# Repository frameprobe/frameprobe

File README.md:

# frameprobe

End-to-end display latency measurement: the time from a mouse input (click or
movement) to a visible change on screen, measured with a photodiode strapped to
the monitor.

**How it works:**

- An RP2040 sends a USB HID mouse click (or, in move mode, a mouse movement)
- The input causes a brightness change on the monitor under test (any application works, as long as the brightness difference is big enough)
- The photodiode picks up the change
- The RP2040 streams ADC samples over serial
- The host logs them to CSV
- `analyze.py` computes the latency

## Components

| Component | Path | Description |
|---|---|---|
| Hardware | `hardware/` | KiCad 10 PCB source (`hardware/pcb/`) and 3D-printable enclosure for the sensor (VBPW34S photodiode + TLV9061 transimpedance amplifier). |
| Firmware | `arduino/` | Runs on any RP2040 board. Fires the mouse input (click, or a single 16-bit HID move report in move mode), samples the photodiode on A1 (14-bit ADC, 12,000 samples per run), sends results as CSV lines over serial. |
| Host software | `main.py` | Interactive serial terminal. Starts/stops test runs, configures measurement mode, click count and interval, logs device data to `output/*.csv`. |
| Analyzer | `analyze.py` | Computes latency from session CSVs or whole folders. Reports signal/noise separation, mean ± 95% CI, sd, median, p5, p95, spread, min, max and an ASCII histogram. Every field is explained in [analyze.md](./analyze.md). |
| Chart data | `analyze_all.py` | Pools each direct subfolder of a results folder and prints chart-ready JSON (medians with error bars, plus shared-bin histograms) for comparing test cases. |
| Reference data | `test_run1/` | Captures and notes from an X11-vs-Wayland test matrix on a 500 Hz QD-OLED (`test_setup.md`, `test_matrix.md`). Done with Perfboard-era sensor, use `-t 100` to reproduce the published numbers. |

## Images

## Host software CLI (`main.py`)

Auto-detects the device by USB VID/PID and provides an interactive prompt. Pass a port
as the first argument to override the search (`uv run main.py /dev/ttyACM1`).

| Command | Description |
|---|---|
| `start` | Start a test session (3s countdown). Logs to `output/<timestamp>_session.csv`. |
| `stop` | Stop the test and close the session CSV. |
| `debug`, `d` | Enable debug mode: device streams raw ADC readings and voltage. |
| `interval <float>`, `i <float>` | Set the time between measurements in seconds (default 0.5). |
| `clicks <int>`, `c <int>` | Set the number of measurements per session (default 10). |
| `mode <click\|move>`, `m <...>` | Set the measurement mode (default `click`). |
| `distance <1-32767>`, `x <int>` | Move mode: distance in HID counts, sent as one atomic report (default 500). |
| `direction <up\|down\|left\|right>`, `r <...>` | Move mode: direction (default `right`). |
| `test`, `t` | Move mode: Fire one visible move with the current settings, then move back after 1s. |
| `connect` / `disconnect` | Open / close the serial connection. |
| `help` | Show the command list. |
| `exit`, `quit` | Disconnect and quit. |

## Measurement modes

- **Click** (default): each measurement is a left mouse click, e.g. a muzzle
  flash in a game, or an app that toggles the screen color on click.
- **Move**: each measurement is a single mouse movement, e.g. camera turns in
  a game. After each measurement the firmware moves the cursor back to where it started.

## Usage

`main.py` and `analyze.py` run on macOS, Linux and Windows.

Before starting a session, run an application on the PC under test in
which the mouse input causes a sufficiently large brightness change.

```sh
uv sync                     # set up Python environment
uv run main.py              # connect to the device, then type: start
uv run main.py COM5         # might be needed in Windows if COM port auto-detect fails
uv run analyze.py output/<session>.csv
uv run analyze.py output/   # or pool a whole folder of sessions
```

By default, `analyze.py` automatically calibrates based on the given input files.

## Test run

`test_run1/` contains methodology and results of the testing I did for a blog post: [Measuring input latency on Linux: X11 vs Wayland, VRR, and DXVK](https://marco-nett.de/blog/measuring-input-latency-on-linux-x11-vs-wayland-vrr-dxvk/).

This test run was done with a proof-of-concept design of the PCB with less sensitivity. To replicate the results from the blog post exactly, use the analyzer with its historical threshold of 100, for example: `uv run analyze.py test_run1/output/1_x11_ll-ON_vrr-ON -t 100`.

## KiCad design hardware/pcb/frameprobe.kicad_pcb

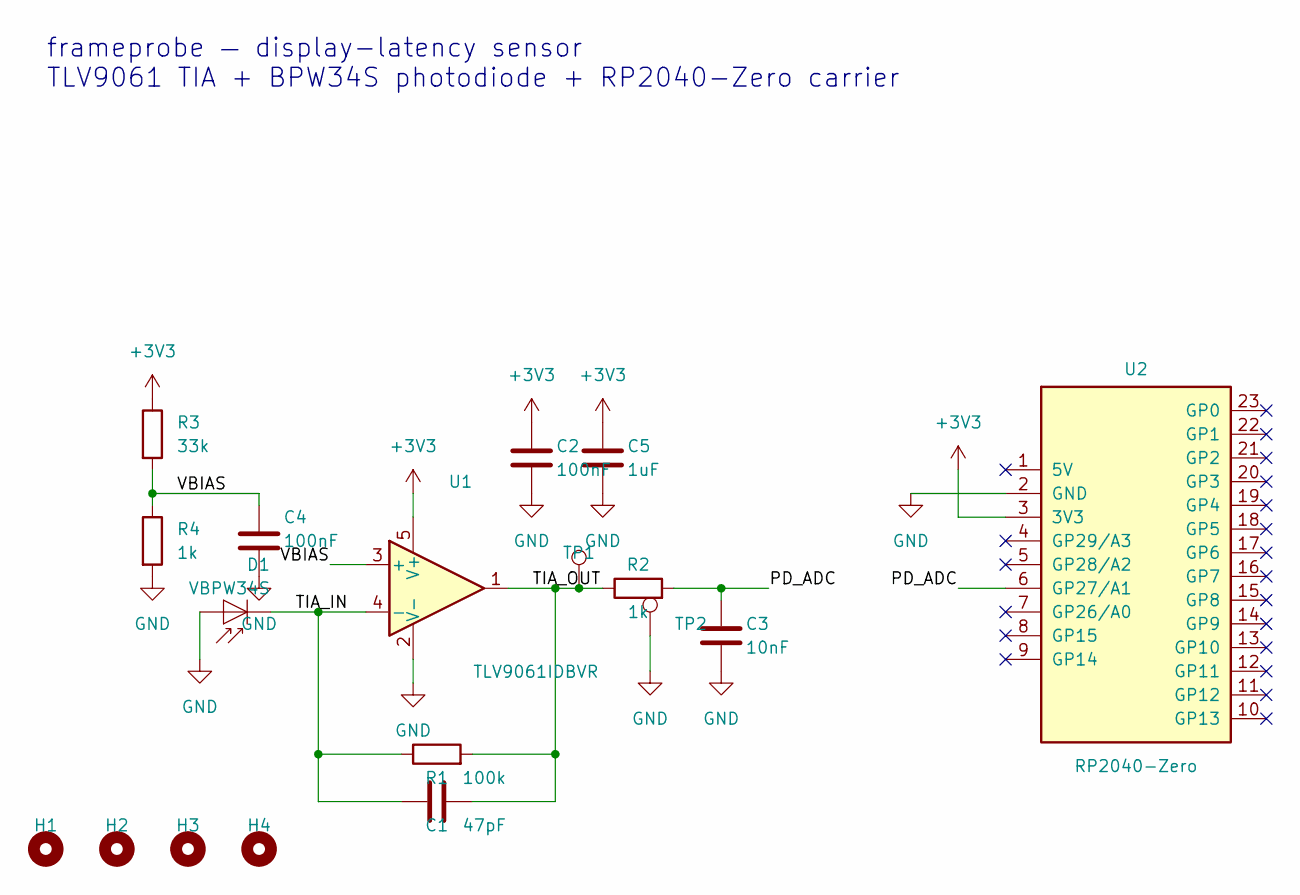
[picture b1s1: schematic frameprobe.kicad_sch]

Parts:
C1: 47pF; C_0603_1608Metric; LCSC C1671
C2, C4: 100nF; C_0603_1608Metric; LCSC C14663
C3: 10nF; C_0603_1608Metric; LCSC C57112
C5: 1uF; C_0603_1608Metric; LCSC C15849
D1: VBPW34S; LCSC C145262
H1, H2, H3, H4: MountingHole; MountingHole_2.1mm
R1: 100k; R_0603_1608Metric; LCSC C25803
R2, R4: 1k; R_0603_1608Metric; LCSC C21190
R3: 33k; R_0603_1608Metric; LCSC C4216
TP1: TIA_OUT; TestPoint_Pad_1.0x1.0mm
TP2: GND; TestPoint_Pad_1.0x1.0mm
U1: TLV9061IDBVR; SOT-23-5; LCSC C398358
U2: RP2040-Zero; RP2040-Zero_THT

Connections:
+3V3: C2.1, C5.1, R3.1, U1.5 (V+), U2.3 (3V3)
/PD_ADC: C3.1, R2.2, U2.6 (GP27/A1)
/TIA_IN: C1.1, D1.2 (K), R1.1, U1.4 (-)
/TIA_OUT: C1.2, R1.2, R2.1, TP1.1, U1.1
/VBIAS: C4.1, R3.2, R4.1, U1.3 (+)
GND: C2.2, C3.2, C4.2, C5.2, D1.1 (A), R4.2, TP2.1, U1.2 (V-), U2.2 (GND)

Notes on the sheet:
frameprobe — display-latency sensor TLV9061 TIA + BPW34S photodiode + RP2040-Zero carrier

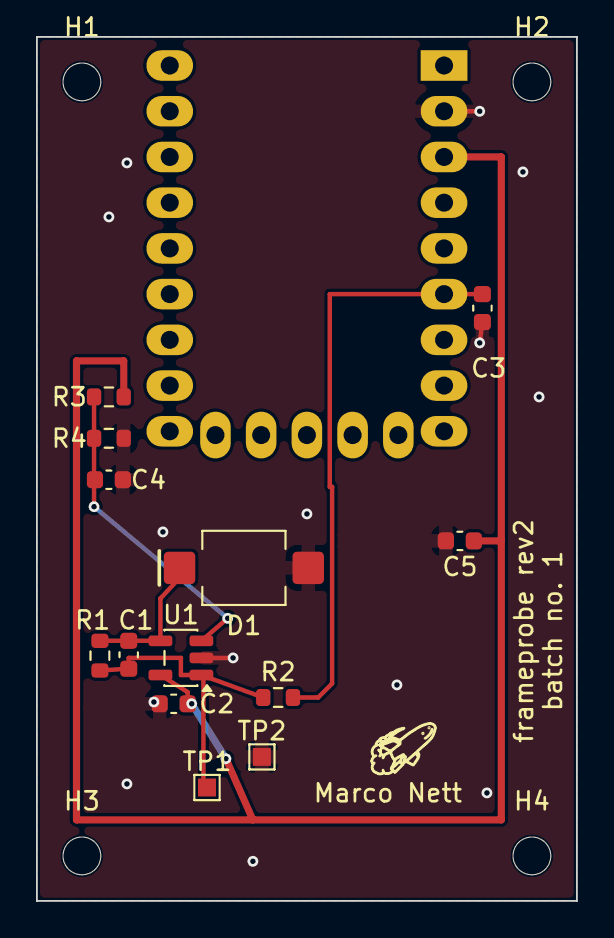
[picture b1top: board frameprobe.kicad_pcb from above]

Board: 2 copper layers, 30.0 x 48.0 mm, 18 parts (1 on the bottom side), 6 nets.
